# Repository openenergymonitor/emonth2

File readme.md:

# emonTH V2.0

**Low power wireless temperature and humidity node**

*V2.0 hardware revision adds support for SI7021 temperature and humidity. This sensor brings performance and power savings over the DHT22, see [sensor](sensor) folder of this repo for sensor evaluation and comparison.*

The emonTH V2 is an open-source, wireless, battery powered temperature and humidity monitoring node.

Data from the emonTH is transmitted via wireless RF (433MHz) to an emonPi / emonBase web-connected base-station for logging to Emoncms for data logging, processing and graphing.

## Documentation

- [Overview](https://docs.openenergymonitor.org/emonth2/overview.html)
- [Installation](https://docs.openenergymonitor.org/emonth2/install.html)
- [Firmware](https://docs.openenergymonitor.org/emonth2/firmware.html)
- [Configuration](https://docs.openenergymonitor.org/emonth2/configuration.html)
- [Technical](https://docs.openenergymonitor.org/emonth2/technical.html)

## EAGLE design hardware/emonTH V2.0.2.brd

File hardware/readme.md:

# Board

# Schematic

# Change log

## V2.0.2 (26th Sep 2016)

- Fix LED trace

## V2.0.1 (Aug 2016)

- Add SI7021 temperature & humidity sensor (see `si7021_eval` folder in emonth2 repo)
- Re-jig port map from emonTH V1.5 to make available I2C pins for SI7021

# Port Map

|                |           |            |                       |
|----------------|-----------|------------|-----------------------|
| Arduino        | ATmega328 | Function   | emonTH V2             |
| Analog 0 (D14) | PC0       |            |                       |
| Analog 1 (D15) | PC1       |            | 2x AA Battery Voltage |
| Analog 2 (D16) | PC2       |            | DHT22 Data            |
| Analog 3 (D17) | PC3       |            | DS18B20 One-wire Data |
| Analog 4 (D18) | PC4       | (SDA)      | SI7021 SDA (Data)     |
| Analog 5 (D19) | PC5       | (SCL)      | SI7021 SCL (SCK)      |
| Analog 6 (D20) |           |            |                       |
| Analog 7 (D21) |           |            |                       |
| Digital 0      | PD0       | (RXD)      | FTDI Tx               |
| Digital 1      | PD1       | (TXD)      | FTDI Rx               |
| Digital 2      | PD2       | (int0) PWM | RFM69CW IRQ           |
| Digital 3      | PD3       | (int1) PWM | Terminal block        |
| Digital 4      | PD4       |            |                       |
| Digital 5      | PD5       | PWM        | DS18B20 PWR           |
| Digital 6      | PD6       | PWM        | DHT22 PWR             |
| Digital 7      | PD7       |            | DIP 1                 |
| Digital 8      | PB0       |            | DIP 2                 |
| Digital 9      | PB1       | PWM        | LED                   |
| Digital 10     | PB2       | (SS) PWM   | RFM69CW SEL           |
| Digital 11     | PB3       | (MOSI) PWM | RFM69CW SDI           |
| Digital 12     | PB4       | (MISO)     | RFM69CW SDO           |
| Digital 13     | PB5       | (SCK)      | RFM69CW SCK           |

# BOM

|Qty |Value                |Device               |Package         |Parts          |Description                                                            |
|----|---------------------|---------------------|----------------|---------------|-----------------------------------------------------------------------|
|1   |                     |ANTENNA              |PAD-01          |ANT1           |Antenna                                                                |
|1   |                     |LEDCHIPLED-0603-TTW  |CHIPLED-0603-TTW|LED            |LED                                                                    |
|4   |0.1uF                |C-EUC0603            |C0603           |C3, C6, C8, C12|CAPACITOR, European symbol                                             |
|2   |0R                   |R-EU_R0603           |R0603           |R2, R3         |RESISTOR, European symbol                                              |
|1   |100K                 |R-EU_R0603           |R0603           |R5             |RESISTOR, European symbol                                              |
|2   |100nF                |C-EUC0603            |C0603           |C9, C10        |CAPACITOR, European symbol                                             |
|1   |10K                  |R-EU_R0603           |R0603           |R1             |RESISTOR, European symbol                                              |
|1   |10K                  |R-US_R0603           |R0603           |R32            |RESISTOR, American symbol                                              |
|1   |10uF                 |C-EUC0603            |C0603           |C5             |CAPACITOR, European symbol                                             |
|1   |10uH                 |INDUCTOR1210         |1210            |L1             |Inductors                                                              |
|1   |16Mhz                |CRYSTALHC49UP        |HC49UP          |Q1             |CRYSTAL                                                                |
|1   |1K                   |R-EU_R0603           |R0603           |R10            |RESISTOR, European symbol                                              |
|3   |1X2-3.5MM            |1X2-3.5MM            |1X2-3.5MM       |J1, J2, J3     |3.5mm Terminal block                                                   |
|3   |1uF                  |C-EUC0603            |C0603           |C1, C2, C4     |CAPACITOR, European symbol                                             |
|2   |22pF                 |C-EUC0603            |C0603           |C7, C11        |CAPACITOR, European symbol                                             |
|1   |2_SMT_DIP_SWITCH     |2_SMT_DIP_SWITCH     |DIP_SWITCH_SMT  |S3             |Multicomp MCEMR-02-T                                                   |
|1   |2x3                  |AVR_SPI_PRG_6PTH     |2X3             |ISP            |AVR ISP 6 Pin                                                          |
|1   |3V                   |3X_AAA_BATTERY_HOLDER|AAA_PCB_HOLDER  |U$3            |2x AA Battery Holder                                                   |
|3   |4K7                  |R-EU_R0603           |R0603           |R4, R6, R24    |RESISTOR, European symbol                                              |
|1   |ATMEGA168MLF         |ATMEGA168MLF         |MLF32           |U1_MLF         |Atmel 32-pin 8-bit micro, 16k flash.                                   |
|1   |ATMEGA328P           |ATMEGA328_SMT        |TQFP32-08       |U1_TQFP        |32-Pin Atmega328 part                                                  |
|1   |DS18B20              |TRANSISTOR_NPNTO92   |TO-92           |Q2             |Transistor NPN                                                         |
|3   |FIDUCIAL             |FIDUCIAL             |FIDUCIAL_1MM    |U$1, U$6, U$7  |For use by pick and place machines to calibrate the vision/machine, 1mm|
|1   |FTDI                 |FTDI_BASICPTH        |FTDI_BASIC      |JP1            |FTDI Basic: 3.3V and 5V                                                |
|1   |LTC3525ESC6-3.3TRMPBF|LTC3525ESC6-3.3TRMPBF|SOT65P210X100-6N|U1             |Step-Up DC/DC Converter                                                |
|1   |RF-LINK_TX           |RF-LINK_TX           |RF-LINK_TX      |U$2            |                                                                       |
|1   |RFM12B               |RFM12B               |RFM12B          |RFM69CW        |                                                                       |
|1   |SI7021               |SI7021               |SI7021          |U2             |The Si7021 is an I2C Humidity and Temperature Sensor                   |
|1   |SMA_EDGE             |SMA_EDGE             |SMA-EDGE        |J$1            |SMA Antenna Connector                                                  |
|1   |SOLDERJUMPERNO       |SOLDERJUMPERNO       |SJ_2S-NO        |SJ1            |Solder Jumper                                                          |
|1   |TOREX XC6206P332MR   |MCP1700T-3302E/TT    |SOT95P237X112-3N|VREG           |Low Quiescent Current LDO                                              |
|1   |USB-MINIB-5PIN       |USB-MINIB-5PIN       |USB-MINIB-CISECO|U$5            |Mini-USB "B" connector with 5th pin broken out.                        |

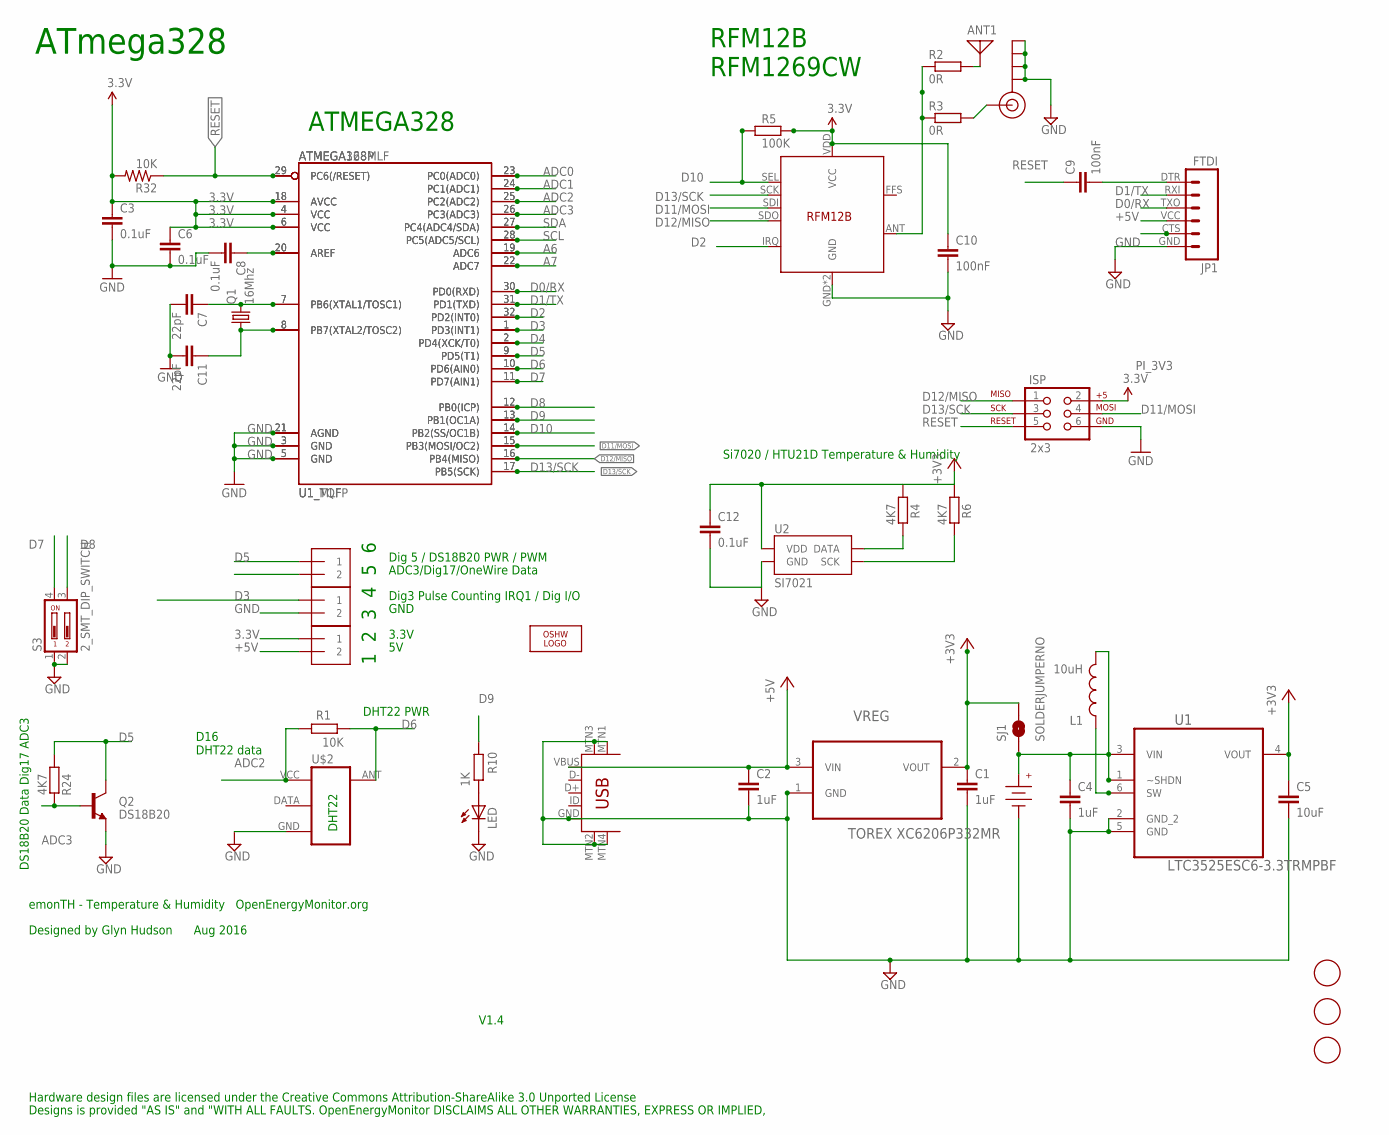
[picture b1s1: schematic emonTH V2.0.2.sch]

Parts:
ANT1: ANTENNA; PAD-01
C1, C2, C4: 1uF; C0603
C3, C6, C8, C12: 0.1uF; C0603
C5: 10uF; C0603
C7, C11: 22pF; C0603
C9, C10: 100nF; C0603
ISP: 2x3; 2X3
J1, J2, J3: 1X2-3.5MM
J$1: SMA_EDGE; SMA-EDGE
JP1: FTDI; FTDI_BASIC
L1: 10uH; 1210
LED: LEDCHIPLED-0603-TTW; CHIPLED-0603-TTW
LOGO2: OSHW_LOGO_10MILX0200-NT; OSHW_10X200_NOTEXT
Q1: 16Mhz; HC49UP
Q2: DS18B20; TO-92
R1, R32: 10K; R0603
R2, R3: 0R; R0603
R4, R6, R24: 4K7; R0603
R5: 100K; R0603
R10: 1K; R0603
RFM69CW: RFM12B
S3: 2_SMT_DIP_SWITCH; DIP_SWITCH_SMT
SJ1: SOLDERJUMPERNO; SJ_2S-NO
U1: LTC3525ESC6-3.3TRMPBF; SOT65P210X100-6N
U1_MLF: ATMEGA168MLF; MLF32
U1_TQFP: ATMEGA328P; TQFP32-08
U2: SI7021
U$1, U$6, U$7: FIDUCIAL; FIDUCIAL_1MM
U$2: RF-LINK_TX
U$3: 3V; AAA_PCB_HOLDER
U$5: USB-MINIB-5PIN; USB-MINIB-CISECO
VREG: TOREX XC6206P332MR; SOT95P237X112-3N

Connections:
3.3V: C1.1, C3.1, C5.1, C6.1, C10.1, C12.1, ISP.2, J3.1, R4.1, R5.2, R6.1, R32.2, RFM69CW.VDD (VCC), SJ1.2, U1.4 (VOUT), U1_MLF.4 (VCC), U1_MLF.6 (VCC), U1_MLF.18 (AVCC), U1_TQFP.4 (VCC), U1_TQFP.6 (VCC), U1_TQFP.18 (AVCC), U2.VDD, VREG.2 (VOUT)
+5V: C2.1, J3.2, JP1.VCC (4), U$5.VBUS, VREG.3 (VIN)
A6: U1_MLF.19 (ADC6), U1_TQFP.19 (ADC6)
A7: U1_MLF.22 (ADC7), U1_TQFP.22 (ADC7)
ADC0: U1_MLF.23 (PC0(ADC0)), U1_TQFP.23 (PC0(ADC0))
ADC1: C4.1, L1.2, SJ1.1, U1.1 (~SHDN), U1.3 (VIN), U1_MLF.24 (PC1(ADC1)), U1_TQFP.24 (PC1(ADC1)), U$3.+
ADC2: R1.2, U1_MLF.25 (PC2(ADC2)), U1_TQFP.25 (PC2(ADC2)), U$2.VCC (+5V)
ADC3: J1.2, Q2.2 (B), R24.2, U1_MLF.26 (PC3(ADC3)), U1_TQFP.26 (PC3(ADC3))
D0/RX: JP1.TXO (3), U1_MLF.30 (PD0(RXD)), U1_TQFP.30 (PD0(RXD))
D1/TX: JP1.RXI (2), U1_MLF.31 (PD1(TXD)), U1_TQFP.31 (PD1(TXD))
D2: RFM69CW.IRQ, U1_MLF.32 (PD2(INT0)), U1_TQFP.32 (PD2(INT0))
D3: J2.1, U1_MLF.1 (PD3(INT1)), U1_TQFP.1 (PD3(INT1))
D4: U1_MLF.2 (PD4(XCK/T0)), U1_TQFP.2 (PD4(XCK/T0))
D5: J1.1, Q2.3 (C), R24.1, U1_MLF.9 (PD5(T1)), U1_TQFP.9 (PD5(T1))
D6: R1.1, U1_MLF.10 (PD6(AIN0)), U1_TQFP.10 (PD6(AIN0)), U$2.ANT
D7: S3.4, U1_MLF.11 (PD7(AIN1)), U1_TQFP.11 (PD7(AIN1))
D8: S3.3, U1_MLF.12 (PB0(ICP)), U1_TQFP.12 (PB0(ICP))
D9: R10.2, U1_MLF.13 (PB1(OC1A)), U1_TQFP.13 (PB1(OC1A))
D10: R5.1, RFM69CW.SEL, U1_MLF.14 (PB2(SS/OC1B)), U1_TQFP.14 (PB2(SS/OC1B))
D11/MOSI: ISP.4, RFM69CW.SDI, U1_MLF.15 (PB3(MOSI/OC2)), U1_TQFP.15 (PB3(MOSI/OC2))
D12/MISO: ISP.1, RFM69CW.SDO, U1_MLF.16 (PB4(MISO)), U1_TQFP.16 (PB4(MISO))
D13/SCK: ISP.3, RFM69CW.SCK, U1_MLF.17 (PB5(SCK)), U1_TQFP.17 (PB5(SCK))
DIG1: R2.1, R3.1, RFM69CW.ANT
GND: C1.2, C2.2, C3.2, C4.2, C5.2, C6.2, C7.2, C8.2, C10.2, C11.2, C12.2, ISP.6, J2.2, J$1.GND@0 (GND), J$1.GND@1 (GND), J$1.GND@2 (GND), J$1.GND@3 (GND), JP1.GND (6), LED.C, Q2.1 (E), RFM69CW.GND, RFM69CW.P$12 (GND), S3.1, S3.2, U1.2 (GND_2), U1.5 (GND), U1_MLF.3 (GND), U1_MLF.5 (GND), U1_MLF.21 (AGND), U1_TQFP.3 (GND), U1_TQFP.5 (GND), U1_TQFP.21 (AGND), U2.GND, U$2.GND, U$3.-, U$5.GND, U$5.MTN1 (MTN2), U$5.MTN2 (MTN3), U$5.MTN3 (MTN1), U$5.MTN4, VREG.1 (GND)
unnamed: LED.A, R10.1
unnamed: C7.1, Q1.2, U1_MLF.7 (PB6(XTAL1/TOSC1)), U1_TQFP.7 (PB6(XTAL1/TOSC1))
unnamed: L1.1, U1.6 (SW)
unnamed: C11.1, Q1.1, U1_MLF.8 (PB7(XTAL2/TOSC2)), U1_TQFP.8 (PB7(XTAL2/TOSC2))
unnamed: ANT1.1, R2.2
unnamed: C8.1, U1_MLF.20 (AREF), U1_TQFP.20 (AREF)
unnamed: C9.2, JP1.DTR (1)
unnamed: J$1.SIG (SIGNAL), R3.2
RESET: C9.1, ISP.5, R32.1, U1_MLF.29 (PC6(/RESET)), U1_TQFP.29 (PC6(/RESET))
SCL: R6.2, U1_MLF.28 (PC5(ADC5/SCL)), U1_TQFP.28 (PC5(ADC5/SCL)), U2.SCK
SDA: R4.2, U1_MLF.27 (PC4(ADC4/SDA)), U1_TQFP.27 (PC4(ADC4/SDA)), U2.DATA

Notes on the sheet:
emonTH - Temperature & Humidity OpenEnergyMonitor.org
Designed by Glyn Hudson Aug 2016
V1.4
DS18B20 Data Dig17 ADC3
ADC3/Dig17/OneWire Data
Dig 5 / DS18B20 PWR / PWM
Dig3 Pulse Counting IRQ1 / Dig I/O
GND
3.3V
DHT22
1 2 3 4 5 6
Hardware design files are licensed under the Creative Commons Attribution-ShareAlike 3.0 Unported License
Designs is provided "AS IS" and "WITH ALL FAULTS. OpenEnergyMonitor DISCLAIMS ALL OTHER WARRANTIES, EXPRESS OR IMPLIED,
ATmega328
ATMEGA328
RFM12B RFM1269CW
D16 DHT22 data
Si7020 / HTU21D Temperature & Humidity
DHT22 PWR

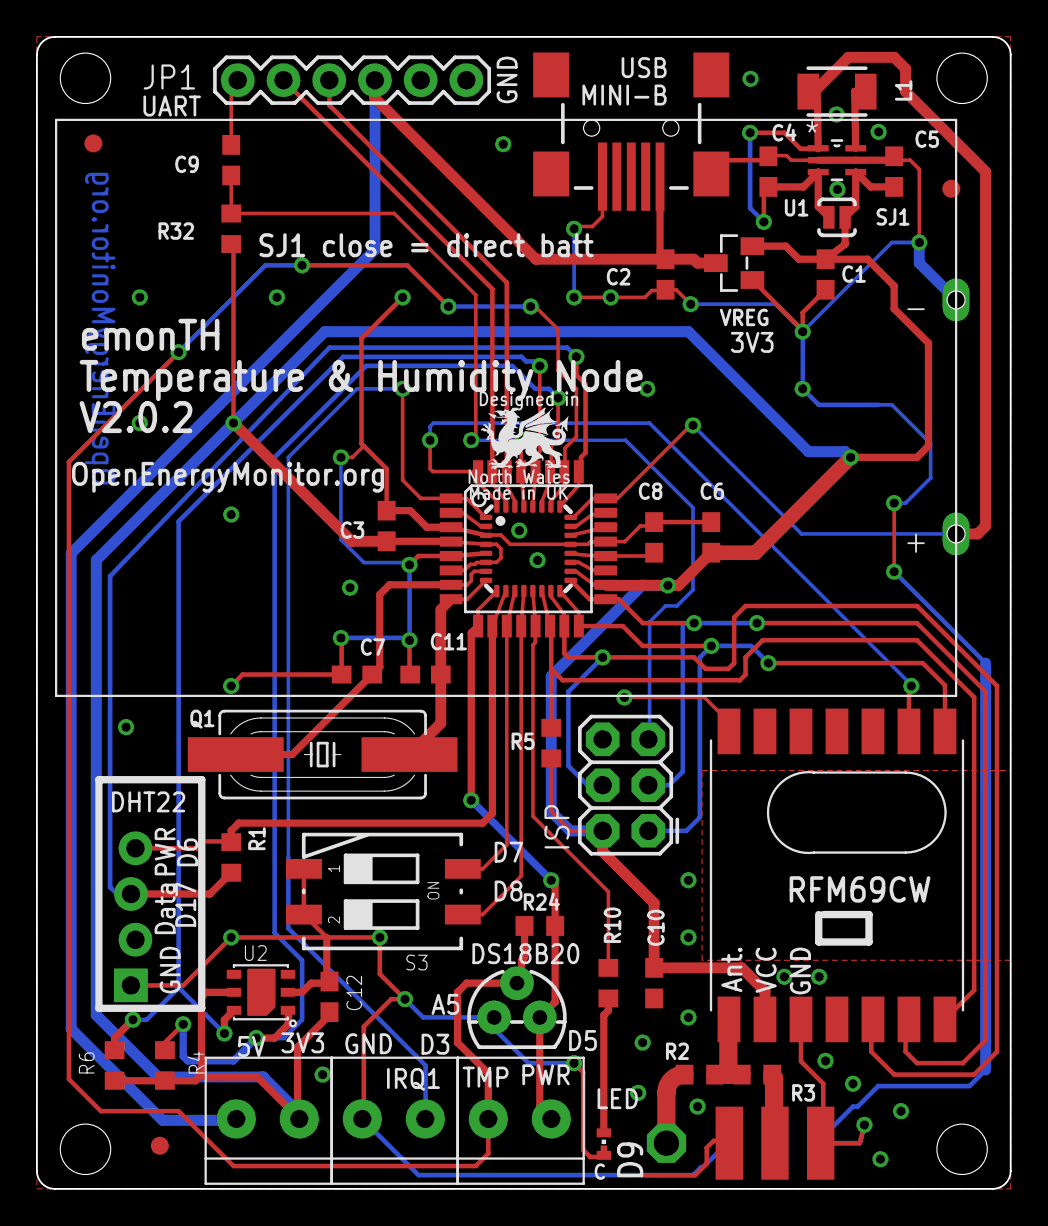
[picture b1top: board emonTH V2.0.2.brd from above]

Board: 2 copper layers, 54.1 x 64.0 mm, 47 parts (1 on the bottom side), 35 nets.

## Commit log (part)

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2016-09-20 first commit fimware for emonTH V2.0 firmware
2016-09-20 add sensor test & readme
2016-09-20 v2.0 readme
2016-09-20 add datasheets
2016-09-21 add travis config
2016-09-21 add unit test 1st draft
2016-09-24 add hardware
2016-09-24 add hardware readme
2016-09-24 crop brd fix bom
2016-09-26 add emonth v2.0.2
2016-09-26 tested working! strip out DHT22 code
2016-09-26 add v2.0.2 gerbers
2016-09-26 correct DH18B20 pin number
2016-09-26 emonth v2 hardware comment
2016-09-28 battey optimisations
2016-09-28 power tweak & add power trace
2016-09-28 remove debug code
2016-09-29 refactor repo structure
2016-09-29 unused inputs configure as input pull-up for low power
2016-09-30 update portmap & sch + brd img
2016-09-30 minor typos
2016-09-30 fix variable decleration
2016-10-01 add battery life calcs
2016-10-02 shorten RFM wakeup time
2016-10-04 re-do emonthv2 battery life estimate, batteris are in series :-)
2016-10-04 Revert "re-do emonthv2 battery life estimate, batteris are in series :-)"
    This reverts commit 3dbadf6331d72acecde24984a721b79868487637.
2016-10-04 battery capacity is 2xAA because of boost converter
2016-10-12 fix lib deps
2016-10-12 add RF to unit test
2016-10-18 travis deploy
2016-10-18 fix travis.yml indentation
2016-10-18 add travis build logo
2016-10-18 fix firmware deploy URL
2016-10-18 add tag condition
2016-10-18 improve error checking
2016-10-18 check for RFM69CW
2016-10-18 bump pio build version
2016-10-30 correct calc energy consumed
2016-11-13 correct energy consumed per day calcs
2016-11-13 add RF serial config feature
2016-11-13 tidy
2016-11-13 add serial config file
2016-11-14 add fab file
2016-11-15 fix and test RF serial config
2016-11-15 RF Serial Config Feature/serialconfig (#1)
    Configure RF config via serial. Ported from recent emonTx V3 update
    https://community.openenergymonitor.org/t/emontx-v3-configure-rf-settings-via-serial-released-fw-v2-6-0/2064
2016-11-16 skip cleanup for deploy
2016-11-29 add board photo
2016-11-29 add photo to readme
2016-11-30 emonth2 blog
2016-11-30 Fix typo
2016-11-30 bump version V3.2.1
2017-01-17 add emonth2 octopart bom
2017-05-12 V3.2.2 fix DIP switches not being read when EEPROM is configured
2017-05-12 fix 3 digit version numbers
2017-07-17 Fix DIP switch had no effect
2017-07-17 don't devide version number in config function
2017-07-26 Fix DIP switch had no effect (#2)
    * Fix DIP switch had no effect
    * don't devide version number in config function
2017-08-09 add custom battery save compiled hex
2017-08-09 rename custom battery fw
2017-10-06 correct emonhub node decoder for custom fw
2018-02-05 add emonupload
2018-05-25 Both NL & CR prompt
2018-05-25 bump version V3.24
2018-10-26 define monitor baud
2020-04-23 fix potential issue with case statement
2021-02-05 support for multiple external temperature sensors
2021-02-28 Added 'showString' to enable use of Arduino IDE
2021-09-20 update platformio
2021-09-20 inc version
2021-10-03 v3.2.6
2023-01-23 emonth2 documentation moved from guide and wiki
2023-01-25 fix links
2023-02-15 ignore pio
2023-02-16 changes for my project to work
2023-02-17 new emonth2 firmware
2023-02-17 single external temperature sensor by default
2023-02-20 Fix missing frequency initialization
2023-02-20 Rename variables
2023-02-27 Add possibility to use custom encrypted key
2023-06-01 add build env for LPL and JeeLib classic RF formats
2023-06-05 Serial print tweaks to enable factory test
2023-06-08 V4.1.3 serial print factory test optimisations
2023-06-08 more serial tweaks
2023-07-21 serial print RF format
2023-07-21 fix lib versions
2023-08-18 Update overview.md
    Add "buy in shop" link.
2023-08-18 Update install.md
    Add "buy in shop" link.
2023-08-21 Update emonth2.ino
    fix set address on LPL
2023-08-21 update change log
2023-08-21 Bump V4.1.5
2023-09-03 increase config delay to 4s fix #21
2023-09-04 add cr after version number (test commit)
2023-09-04 serial config timeout fixes and improved error checking
2023-09-20 Prevent dip switch pullups drawing power if switches closed
2023-09-20 Prevent dip switch pullups drawing power if switches closed (#25)
2024-02-26 V4.1.6 Fix DS18B20 serial printing & multiple sensors
2024-02-26 add example node decoders
2024-02-26 lower case
2024-03-05 V4.1.7 fix DIP swich nodeID config
2024-07-15 Handle si7021 returning negative humidity
    `si7021_env::humidityBasisPoints` is `unsigned int`, but `SI7021::getHumidityBasisPoints` is returning a value ranged from -600 ... 11900 inclusive, where negative values will underflow to 64936 ... 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
    `struct Payload::humidity` is signed integer and we don't want to modify si7021 library, so we just pad the value when doing conversion, where calculation is done in (signed) floating point.
2024-07-15 just cast to `int` is enough
2024-07-15 remove extra parenthesis
2025-03-13 repeater code
2025-04-14 updated to use minimal RFM69_LPL library
2025-04-14 remove wait for channel clear
2025-04-14 add latest hex file
2025-08-11 Add documentation about using multiple external temperature probes
2025-11-27 Add documentation about using multiple external temperature probes (#29)
2025-12-09 change default to 433.92 MHz
2025-12-09 precompiled 433.92Mhz firmware
2025-12-09 option to set frequency
2025-12-09 update version

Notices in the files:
parts and their libraries:
SparkFun-DigitalIC: Licensing: CC v3.0 Share-Alike You are welcome to use this library for commercial purposes.
SparkFun-Sensors: Licensing: Creative Commons ShareAlike 4.0 International - https://creativecommons.org/licenses/by-sa/4.0
